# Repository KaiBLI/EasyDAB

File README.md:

# EasyDABv2
Repository of Plain-English Information for Sergiy's EasyDABv2 DAB Exciter Board. This is not to be confused with the EasyDABv1 which is a USB-based DAB exciter board. The USB DAB Board requires a computer to handle modulation while the v2 board utilizes a FPGA for independent operation.

# Introducton
First off, much of this is not my original work, credit goes to Sergiy for the design and release of the EasyDAB board. His site can be found here: https://tipok.org.ua/node/46

Secondly, this is a repository of the information I've learned through trying to manufacture one of these boards myself in order that folks in the future have an easier time with it than me.
There are a couple of issues with the original release of this board, firstly, I have not been able to find a license or any information regarding copyright of this board. Given that this was done in collaboration with the OpenDigitalRadio group, it is assumed that the board was released under similar licensing to the other projects under OpenDigitalRadio, that is permitting deriative work which is also licensed under the GPL and with credit to the original creator. 

If the above is not correct and the board was released under a more restrictive license, please get in touch at hoosk@retrohoosk.tv and this repository will be updated as such. That being said, under no circumstances will documentation of my own making be removed that was created based on information that is publicly available. 

# Aims
As mentioned in the introduction, the information is somewhat sparse on how to go about creating one of these boards. The original release was an Eagle PCB project coupled with a release of the firmware for flashing the board. The rest is left up to the individual to 'figure it out' (tm). 

As I'm a believer in easy, accessible and transparent documentation railing against those that insist on spoon-feeding being a bad thing, I have determined to document my findings and provide as much information as possible regarding the manufacture and configuration of these boards. 

So the aims of this project encompass the following:
1. Documentation

I will proceed to create an 'info dump' of all of my findings that I've learned through building this projects.

2. Photos

I will proceed to create high-resolution and detailed photos of both empty boards and fully assembled units so that others can see what these look like once assembled.

3. A fresh bill of materials.

The existing bill of materials leave too much up to assumption, therefore I will create a digikey cart and an Excel sheet of components required including example part numbers. It is assumed that components over time will be obsoleted and substitutes will be required, hence specification of components will be detailed as possible.

4. New Features

The board already supports DRM and FM modulation in addition to DAB/DAB+, theortically additional FPGA core/firmware could be built for other digital modulation such as HDRadio/NRSC5 and DVB. 

5. Board redesign.

The existing board requires redesign, solder pads overlay over existing component lables, requiring continuous reference to the PCB layout in CAD during assembly. This leaves opportunity to mistake and damage of expensive components (I'm looking at that Analog Devices Digital Synthesiser!). The board also allows different options depending on whether you wish to use a Single Frequency Network, FM or Digital Radio Mondiale usage, whether to use the mini360 modules and whether to use the band-pass filter. Given that there is little need for this board to be compact, outside of manufactoring costs, additional space can be used to make component locations clearer to the average hobbyist.

# Contact
Questions and Comments can be directed to hoosk@retrohoosk.tv , I'd love to hear your experience with assembling one of these boards and other ideas for this repo.

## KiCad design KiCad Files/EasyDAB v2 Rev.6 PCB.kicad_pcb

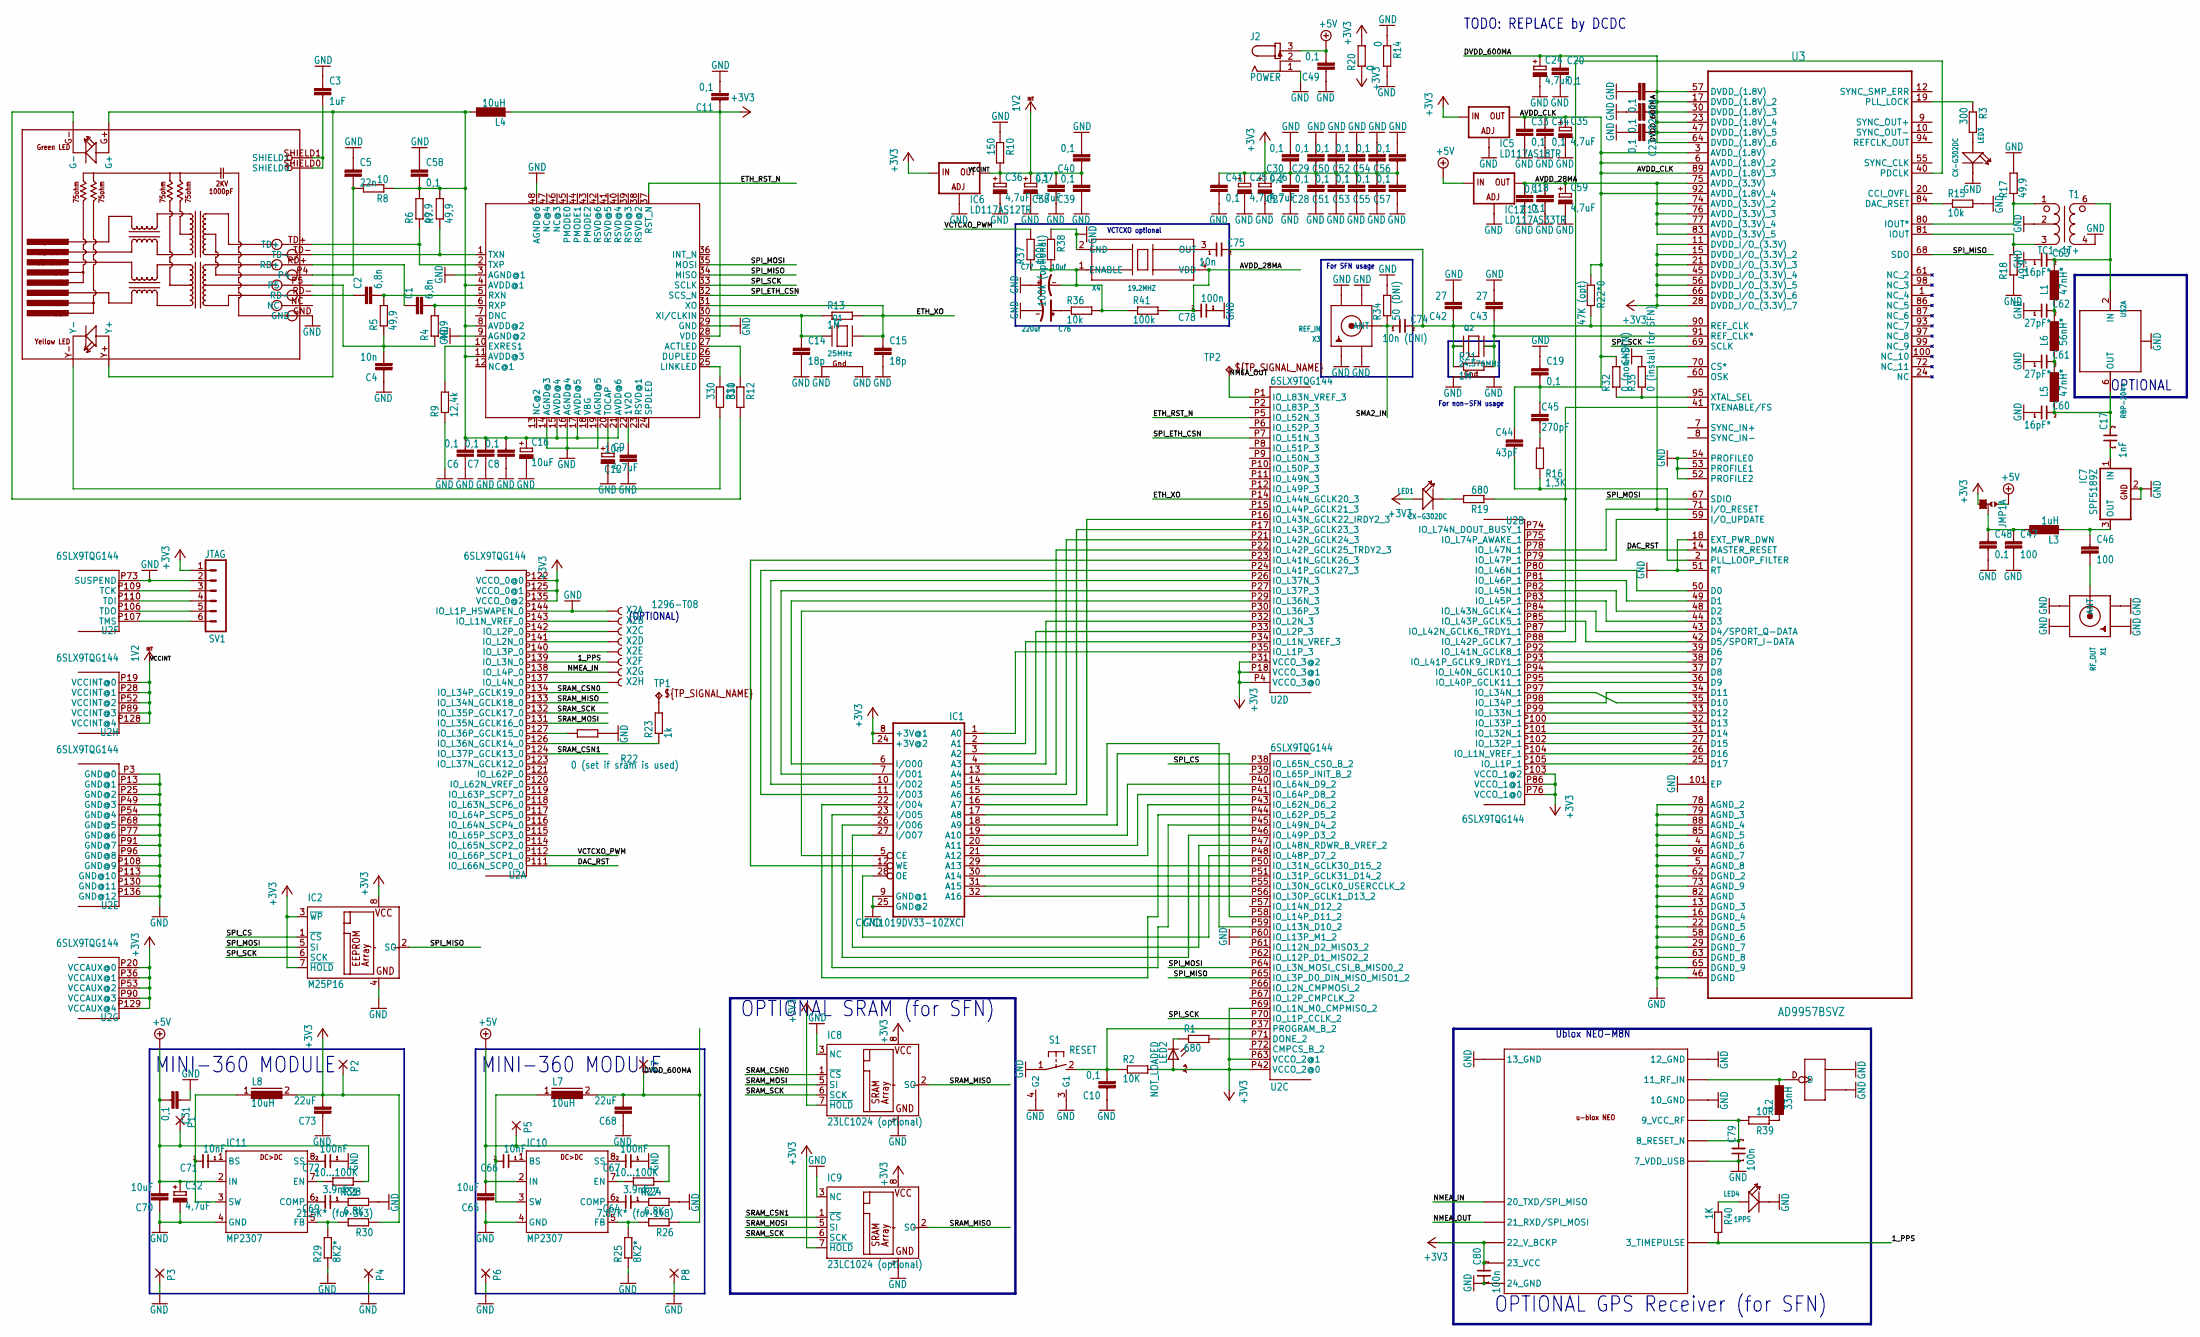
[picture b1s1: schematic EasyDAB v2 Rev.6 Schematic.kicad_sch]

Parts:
ANT1: U-FL; U-FL3P-SMD-2.6X2.6X1.0MM
C1, C2: 6,8n; C0805
C3: 1uF; C1206
C4, C12: 10n; C0805
C5: 22n; C0805
C6, C7, C8, C10, C11, C13, C18, C19, C20, C21, C22, C23, C27, C28, C29, C30, C31, C33, C34, C38, C39, C40, C41, C49, C50, C51, C52, C53, C54, C55, C56, C57, C58: 0,1; C0805
C9, C24, C25, C26, C32, C35, C36, C37, C59: 4,7uF; A_3216-18R
C14, C15: 18p; C0805
C16: 10uF; A_3216-18R
C17: 1nF; 0603
C42, C43: 27; C0805
C44: 43pF; C0805
C45: 270pF; C0805
C46, C47: 100; C0805
C48: 0.1; C0805
C60, C63: 16pF*; 0603
C61, C62: 27pF*; 0603
C64, C69: 3.9nF; 0603
C65, C70: 10uF; C1206
C66, C71: 10nF; 0603
C67, C72: 100nF; 0603
C68, C73: 22uF; C1206
C74: 10n (DNI); 0603
C75: 10n; 0603
C76: 220uf; AVX-D
C77: 10uf; AVX-A
C78, C79, C80: 100n; 0603
IC1: CY7C1019DV33-10ZXCI; TSOPII-32
IC2: M25P16; SO-08
IC5: LD117AS18TR; SOT223
IC6: LD117AS12TR; SOT223
IC7: SPF5189Z; SOT89
IC8, IC9: 23LC1024 (optional); SO-08
IC10, IC11: MP2307; SO8
IC12: LD117AS33TR; SOT223
J2: POWER; SPC4077
JMP1: 0R-JUMPA; A0R-JMP
L1, L5: 47nH*; INDC1608X95N
L2: 33nH; INDC1608X95N
L3: 1uH; L3216C
L4: 10uH; L3216C
L6: 56nH*; INDC1608X95N
L7, L8: 10uH; DR74
LED1, LED3: CX-G302DC; LED2-2.54-D3.0MM
LED2: NOT_LOADED; CHIPLED_1206
LED4: 1PPS; LED2-2.54-D3.0MM
P1, P2, P3, P4, P5, P6, P7, P8: 1,6/0,8; 1,6_0,8
Q1: 25MHz; NX3225
Q2: 24.576MHz; NX3225
R1, R19: 680; M0805
R2: 10K; M0805
R3: 300; M0805
R4, R5, R6, R7, R17, R18: 49,9; R0805
R8: 10; R0805
R9: 12,4k; R0805
R10: 150; R0805
R11, R12: 330; R0805
R13, R21: 1M; R0805
R14: 0; R0805
R15: 10k; R0805
R16: 1,3K; R0805
R20: 0; R1210
R22: 0 (set if sram is used); R0402
R22*0: 47K (opt); R0603
R23: 1k; R0603
R24, R28: 6.8K; R0603
R25, R29: 8K2*; R0603
R26: 7.87K* (for 1v8); R0603
R27, R31: 10...100K; R0603
R30: 21.5K* (for 3v3); R0603
R32: 0 (non-SFN); R0402
R33: 0 (install for SFN); R0402
R34: 50 (DNI); R0402
R36: 10k; R0603
R37, R41: 100k; R0603
R38: 100k (optional); R0603
R39: 10R; R0402
R40: 1K; R0402
RJ2: HR911105A
S1: RESET; B3F-31XX
SV1: JTAG; MA06-1
T1: TC1-1T+; AT224-3
TP1: PPS_IN; B1,27
TP2: UART_OUT; B1,27
U1: W5500
U2: 6SLX9TQG144; TQ144
U3: AD9957BSVZ; QFP50P1600X1600X120-101N
U$1: NEO-M8
U$2: RBP-204+; GP731
X1: RF_OUT; SMA90_DIP
X2: 1296-T08; 1296-08
X3: REF_IN; W5500_LX9_AD9957_SMA_EDGELAUNCH_UFL
X4: 19.2MHZ; X4-SMD-3.2X2.5X0.7MM

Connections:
1_PPS: R40.2, U2.P139 (IO_L3N_0), U$1.3 (3_TIMEPULSE), X2.6
+3V3: C11.1, C25.+, C26.+, C27.2, C28.2, C29.1, C30.1, C41.1, C50.1, C51.2, C52.1, C53.2, C54.1, C55.2, C56.1, C57.2, C73.2, C80.2, IC1.8 (+3V@1), IC1.24 (+3V@2), IC2.3 (~WP), IC2.7 (~HOLD), IC2.8 (VCC), IC5.3 (IN), IC6.3 (IN), IC8.7 (~HOLD), IC8.8 (VCC), IC9.7 (~HOLD), IC9.8 (VCC), JMP1.3, L4.2, L8.2, LED1.A (+), LED2.A, P2.1, R2.2, R20.1, R20.2, R30.1, SV1.1, U1.28 (VDD), U2.P4 (VCCO_3@0), U2.P18 (VCCO_3@1), U2.P20 (VCCAUX@0), U2.P31 (VCCO_3@2), U2.P36 (VCCAUX@1), U2.P42 (VCCO_2@0), U2.P53 (VCCAUX@2), U2.P63 (VCCO_2@1), U2.P69 (IO_L1N_M0_CMPMISO_2), U2.P76 (VCCO_1@0), U2.P86 (VCCO_1@1), U2.P90 (VCCAUX@3), U2.P103 (VCCO_1@2), U2.P122 (VCCO_0@0), U2.P125 (VCCO_0@1), U2.P129 (VCCAUX@4), U2.P135 (VCCO_0@2), U3.11 (DVDD_I/O_(3.3V)), U3.15 (DVDD_I/O_(3.3V)_2), U3.21 (DVDD_I/O_(3.3V)_3), U3.28 (DVDD_I/O_(3.3V)_7), U3.45 (DVDD_I/O_(3.3V)_4), U3.56 (DVDD_I/O_(3.3V)_5), U3.66 (DVDD_I/O_(3.3V)_6), U$1.22 (22_V_BCKP), U$1.23 (23_VCC)
+5V: C31.2, C32.+, C49.2, C65.2, C70.2, IC10.2 (IN), IC11.2 (IN), IC12.3 (IN), J2.3, JMP1.1, P1.1, P5.1, R27.1, R31.1
AVDD_28MA: C13.2, C18.1, C59.+, C78.2, IC12.4 (OUT), R41.2, U3.74 (AVDD_(3.3V)_2), U3.75 (AVDD_(3.3V)), U3.76 (AVDD_(3.3V)_3), U3.77 (AVDD_(3.3V)_4), U3.83 (AVDD_(3.3V)_5), X4.4 (VDD)
AVDD_CLK: C19.2, C33.1, C34.1, C35.+, C44.1, C45.1, IC5.4 (OUT), R22*0.1, R32.2, U3.3 (AVDD_(1.8V)), U3.6 (AVDD_(1.8V)_2), U3.89 (AVDD_(1.8V)_3), U3.92 (AVDD_(1.8V)_4)
AVDD_ETH: C6.2, C7.2, C8.2, C16.+, C58.2, L4.1, R6.2, R7.2, R8.1, RJ2.G+, RJ2.Y+, U1.4 (AVDD@1), U1.8 (AVDD@2), U1.11 (AVDD@3), U1.15 (AVDD@4), U1.17 (AVDD@5), U1.21 (AVDD@6)
DAC_RST: U2.P111 (IO_L66N_SCP0_0), U3.14 (MASTER_RESET)
DVDD_600MA: C20.1, C21.1, C22.1, C23.1, C24.+, C68.2, L7.2, P7.1, R26.1, U3.17 (DVDD_(1.8V)_2), U3.23 (DVDD_(1.8V)_4), U3.30 (DVDD_(1.8V)_3), U3.47 (DVDD_(1.8V)_5), U3.57 (DVDD_(1.8V)), U3.64 (DVDD_(1.8V)_6)
ETH_RST_N: U1.37 (RST_N), U2.P5 (IO_L52N_3)
ETH_XO: C15.1, Q1.3 (X2), R13.2, U1.31 (XO), U2.P14 (IO_L44N_GCLK20_3)
GND: ANT1.GND1, ANT1.GND2, C3.1, C4.1, C5.1, C6.1, C7.1, C8.1, C9.-, C10.1, C11.2, C12.1, C13.1, C14.2, C15.2, C16.-, C18.2, C19.1, C20.2, C21.2, C22.2, C23.2, C24.-, C25.-, C26.-, C27.1, C28.1, C29.2, C30.2, C31.1, C32.-, C33.2, C34.2, C35.-, C36.-, C37.-, C38.1, C39.1, C40.2, C41.2, C42.2, C43.2, C47.2, C48.2, C49.1, C50.2, C51.1, C52.2, C53.1, C54.2, C55.1, C56.2, C57.1, C58.1, C59.-, C60.1, C61.1, C62.1, C63.1, C65.1, C67.1, C68.1, C70.1, C72.1, C73.1, C76.-, C77.+, C78.1, C79.1, C80.1, IC1.9 (GND@1), IC1.25 (GND@2), IC2.4 (GND), IC5.1 (ADJ), IC6.1 (ADJ), IC7.2 (GND), IC7.2@1 (GND@1), IC8.3 (NC), IC8.4 (GND), IC9.3 (NC), IC9.4 (GND), IC10.4 (GND), IC11.4 (GND), IC12.1 (ADJ), J2.1, LED3.K (-), LED4.K (-), P3.1, P4.1, P6.1, P8.1, Q1.2 (G2), Q1.4 (G1), Q2.2 (G2), Q2.4 (G1), R9.1, R10.1, R14.1, R14.2, R15.2, R17.2, R18.1, R22.1, R24.2, R25.1, R28.2, R29.1, R33.2, R34.2, R38.1, RJ2.GND, S1.1, S1.3 (G1), S1.4 (G2), SV1.2, T1.2 (SCT), T1.4, U1.3 (AGND@1), U1.9 (AGND@2), U1.14 (AGND@3), U1.16 (AGND@4), U1.19 (AGND@5), U1.29 (GND), U1.48 (AGND@6), U2.P3 (GND@0), U2.P13 (GND@1), U2.P25 (GND@2), U2.P49 (GND@3), U2.P54 (GND@4), U2.P60 (IO_L13P_M1_2), U2.P68 (GND@5), U2.P73 (SUSPEND), U2.P77 (GND@6), U2.P91 (GND@7), U2.P96 (GND@8), U2.P108 (GND@9), U2.P113 (GND@10), U2.P130 (GND@11), U2.P136 (GND@12), U2.P144 (IO_L1P_HSWAPEN_0), U3.4 (AGND_6), U3.5 (AGND_8), U3.13 (DGND_3), U3.16 (DGND_4), U3.18 (EXT_PWR_DWN), U3.22 (DGND_5), U3.29 (DGND_7), U3.46 (DGND), U3.51 (RT), U3.52 (PROFILE2), U3.53 (PROFILE1), U3.54 (PROFILE0), U3.58 (DGND_6), U3.62 (DGND_2), U3.63 (DGND_8), U3.65 (DGND_9), U3.73 (AGND_9), U3.78 (AGND_2), U3.79 (AGND_3), U3.82 (AGND), U3.85 (AGND_5), U3.88 (AGND_4), U3.96 (AGND_7), U3.101 (EP), U$1.7 (7_VDD_USB), U$1.10 (10_GND), U$1.12 (12_GND), U$1.13 (13_GND), U$1.24 (24_GND), U$2.1 (GND), U$2.3 (GND), U$2.4 (GND), U$2.5 (GND), U$2.7 (GND), U$2.8 (GND), X1.GND1, X1.GND2, X1.GND3, X1.GND4, X2.1, X3.GND@1 (GND1), X3.GND@2 (GND2), X3.GND@3 (GND3), X3.GND@4 (GND4), X4.2 (GND)
unnamed: SV1.6, U2.P107 (TMS)
unnamed: SV1.5, U2.P106 (TDO)
unnamed: SV1.4, U2.P110 (TDI)
unnamed: SV1.3, U2.P109 (TCK)
unnamed: LED2.C, R1.1
unnamed: R1.2, U2.P71 (DONE_2)
unnamed: U2.P105 (IO_L1P_1), U3.25 (D17)
unnamed: C10.2, R2.1, S1.2 (S), U2.P37 (PROGRAM_B_2)
unnamed: U2.P88 (IO_L42P_GCLK7_1), U3.40 (PDCLK)
unnamed: R19.1, U2.P87 (IO_L42N_GCLK6_TRDY1_1), U3.41 (TXENABLE/FS)
unnamed: U2.P85 (IO_L43P_GCLK5_1), U3.42 (D5/SPORT_I-DATA)
unnamed: U2.P84 (IO_L43N_GCLK4_1), U3.43 (D4/SPORT_Q-DATA)
unnamed: U2.P83 (IO_L45P_1), U3.44 (D3)
unnamed: U2.P82 (IO_L45N_1), U3.48 (D2)
unnamed: U2.P92 (IO_L41N_GCLK8_1), U3.39 (D6)
unnamed: U2.P93 (IO_L41P_GCLK9_IRDY1_1), U3.38 (D7)
unnamed: U2.P94 (IO_L40N_GCLK10_1), U3.37 (D8)
unnamed: U2.P95 (IO_L40P_GCLK11_1), U3.36 (D9)
unnamed: U2.P98 (IO_L34P_1), U3.34 (D11)
unnamed: U2.P97 (IO_L34N_1), U3.35 (D10)
unnamed: U2.P99 (IO_L33N_1), U3.33 (D12)
unnamed: U2.P100 (IO_L33P_1), U3.32 (D13)
unnamed: U2.P101 (IO_L32N_1), U3.31 (D14)
unnamed: U2.P102 (IO_L32P_1), U3.27 (D15)
unnamed: U2.P104 (IO_L1N_VREF_1), U3.26 (D16)
unnamed: U2.P79 (IO_L47P_1), U3.59 (I/O_UPDATE)
unnamed: U2.P78 (IO_L47N_1), U3.70 (CS*), U3.71 (I/O_RESET)
unnamed: U2.P81 (IO_L46P_1), U3.49 (D1)
unnamed: LED3.A (+), R3.2
unnamed: R3.1, U3.19 (PLL_LOCK)
unnamed: R15.1, U3.84 (DAC_RSET)
unnamed: R17.1, T1.1 (SD), U3.80 (IOUT*)
unnamed: R18.2, T1.3 (S), U3.81 (IOUT)
unnamed: C63.2, L1.2, T1.6 (PD), U$2.2 (IN)
unnamed: U2.P80 (IO_L46N_1), U3.50 (D0)
unnamed: IC1.32 (A16), U2.P56 (IO_L30P_GCLK1_D13_2)
unnamed: IC1.31 (A15), U2.P55 (IO_L30N_GCLK0_USERCCLK_2)
unnamed: IC1.30 (A14), U2.P51 (IO_L31P_GCLK31_D14_2)
unnamed: IC1.29 (A13), U2.P50 (IO_L31N_GCLK30_D15_2)
unnamed: IC1.28 (OE), U2.P48 (IO_L48P_D7_2)
unnamed: IC1.27 (I/O07), U2.P47 (IO_L48N_RDWR_B_VREF_2)
unnamed: IC1.26 (I/O06), U2.P46 (IO_L49P_D3_2)
unnamed: IC1.1 (A0), U2.P35 (IO_L1P_3)
unnamed: IC1.23 (I/O05), U2.P45 (IO_L49N_D4_2)
unnamed: IC1.22 (I/O04), U2.P44 (IO_L62P_D5_2)
unnamed: IC1.21 (A12), U2.P43 (IO_L62N_D6_2)
unnamed: IC1.20 (A11), U2.P41 (IO_L64P_D8_2)
unnamed: IC1.19 (A10), U2.P40 (IO_L64N_D9_2)
unnamed: IC1.18 (A9), U2.P58 (IO_L14P_D11_2)
unnamed: IC1.17 (A8), U2.P59 (IO_L13N_D10_2)
unnamed: IC1.2 (A1), U2.P34 (IO_L1N_VREF_3)
unnamed: IC1.3 (A2), U2.P33 (IO_L2P_3)
unnamed: IC1.4 (A3), U2.P32 (IO_L2N_3)
unnamed: IC1.13 (A4), U2.P22 (IO_L42P_GCLK25_TRDY2_3)
unnamed: IC1.12 (WE), U2.P23 (IO_L41N_GCLK26_3)
unnamed: IC1.14 (A5), U2.P21 (IO_L42N_GCLK24_3)
unnamed: IC1.15 (A6), U2.P17 (IO_L43P_GCLK23_3)
unnamed: IC1.11 (I/O03), U2.P24 (IO_L41P_GCLK27_3)
unnamed: IC1.10 (I/O02), U2.P26 (IO_L37N_3)
unnamed: IC1.7 (I/O01), U2.P27 (IO_L37P_3)
unnamed: IC1.6 (I/O00), U2.P29 (IO_L36N_3)
unnamed: IC1.16 (A7), U2.P16 (IO_L43N_GCLK22_IRDY2_3)
unnamed: IC1.5 (CE), U2.P30 (IO_L36P_3)
unnamed: R7.1, RJ2.TD-, U1.1 (TXN)
unnamed: R6.1, RJ2.TD+, U1.2 (TXP)
unnamed: C1.1, RJ2.RD+
unnamed: C1.2, R4.2, U1.6 (RXP)
unnamed: C2.2, R5.2, U1.5 (RXN)
unnamed: C2.1, RJ2.RD-
unnamed: C3.2, RJ2.SHIELD0, RJ2.SHIELD1
unnamed: C4.2, R4.1, R5.1, RJ2.P5
unnamed: C12.2, U1.22 (1V2O)
unnamed: C5.2, R8.2, RJ2.P4
unnamed: R22.2, U2.P127 (IO_L36P_GCLK15_0)
unnamed: R23.2, TP1.TP
unnamed: C9.+, U1.20 (TOCAP)
unnamed: C44.2, R16.2, U3.2 (PLL_LOOP_FILTER)
unnamed: R9.2, U1.10 (EXRES1)
unnamed: R11.1, U1.25 (LINKLED)
unnamed: R12.1, U1.27 (ACTLED)
unnamed: R11.2, RJ2.Y-
unnamed: R12.2, RJ2.G-
unnamed: C14.1, Q1.1 (X1), R13.1, U1.30 (XI/CLKIN)
unnamed: C45.2, R16.1
unnamed: C17.2, C60.2, L5.1, U$2.6 (OUT)
unnamed: C46.1, IC7.3 (OUT), L3.2
unnamed: C46.2, X1.ANTENNA (ANT)
unnamed: C47.1, C48.1, JMP1.2, L3.1
unnamed: LED1.K (-), R19.2
unnamed: L2.1, R39.1
unnamed: C61.2, L5.2, L6.1
unnamed: R23.1, U2.P126 (IO_L36N_GCLK14_0)
unnamed: C79.2, R39.2, U$1.8 (8_RESET_N), U$1.9 (9_VCC_RF)
unnamed: LED4.A (+), R40.1
unnamed: U2.P141 (IO_L2N_0), X2.4
unnamed: U2.P140 (IO_L3P_0), X2.5
unnamed: U2.P137 (IO_L4N_0), X2.8
unnamed: C62.2, L1.1, L6.2
unnamed: C17.1, IC7.1 (IN)
unnamed: C64.2, IC10.6 (COMP)
unnamed: C64.1, R24.1
unnamed: C66.1, IC10.1 (BS)
unnamed: C66.2, IC10.3 (SW), L7.1
unnamed: C67.2, IC10.8 (SS)
unnamed: IC10.5 (FB), R25.2, R26.2
unnamed: R32.1, R33.1, U3.95 (XTAL_SEL)
unnamed: IC10.7 (EN), R27.2
unnamed: C69.1, R28.1
unnamed: C69.2, IC11.6 (COMP)
unnamed: C71.1, IC11.1 (BS)
unnamed: C71.2, IC11.3 (SW), L8.1
unnamed: C72.2, IC11.8 (SS)
unnamed: IC11.5 (FB), R29.2, R30.2
unnamed: IC11.7 (EN), R31.2
unnamed: C76.+, R36.1
unnamed: C77.-, R36.2, R37.1, R38.2, R41.1, X4.1 (ENABLE)
unnamed: ANT1.D, L2.2, U$1.11 (11_RF_IN)
unnamed: C75.1, X4.3 (OUT)
NMEA_IN: U2.P138 (IO_L4P_0), U$1.20 (20_TXD/SPI_MISO), X2.7
NMEA_OUT: TP2.TP, U2.P1 (IO_L83N_VREF_3), U$1.21 (21_RXD/SPI_MOSI)
SMA2_IN: C74.1, R34.1, X3.P (ANT)
SPIRAM_PIN: U2.P143 (IO_L1N_VREF_0), X2.2
SPIRAM_PINX: U2.P142 (IO_L2P_0), X2.3
SPI_CS: IC2.1 (~CS), U2.P38 (IO_L65N_CSO_B_2)
SPI_ETH_CSN: U1.32 (SCS_N), U2.P7 (IO_L51N_3)
SPI_MISO: IC2.2 (SO), U1.34 (MISO), U2.P65 (IO_L3P_D0_DIN_MISO_MISO1_2), U3.68 (SDO)
SPI_MOSI: IC2.5 (SI), U1.35 (MOSI), U2.P64 (IO_L3N_MOSI_CSI_B_MISO0_2), U3.67 (SDIO)
SPI_SCK: IC2.6 (SCK), U1.33 (SCLK), U2.P70 (IO_L1P_CCLK_2), U3.69 (SCLK)
SRAM_CSN0: IC8.1 (~CS), U2.P134 (IO_L34P_GCLK19_0)
SRAM_CSN1: IC9.1 (~CS), U2.P124 (IO_L37P_GCLK13_0)
SRAM_MISO: IC8.2 (SO), IC9.2 (SO), U2.P133 (IO_L34N_GCLK18_0)
SRAM_MOSI: IC8.5 (SI), IC9.5 (SI), U2.P131 (IO_L35N_GCLK16_0)
SRAM_SCK: IC8.6 (SCK), IC9.6 (SCK), U2.P132 (IO_L35P_GCLK17_0)
VCCINT: C36.+, C37.+, C38.2, C39.2, C40.1, IC6.4 (OUT), R10.2, U2.P19 (VCCINT@0), U2.P28 (VCCINT@1), U2.P52 (VCCINT@2), U2.P89 (VCCINT@3), U2.P128 (VCCINT@4)
VCTCXO_PWM: R37.2, U2.P112 (IO_L66P_SCP1_0)
XTALI: C42.1, C74.2, C75.2, Q2.1 (X1), R21.1, R22*0.2, U3.90 (REF_CLK)
XTALO: C43.1, Q2.3 (X2), R21.2, U3.91 (REF_CLK*)

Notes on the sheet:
MINI-360 MODULE
Ublox NEO-M8N
OPTIONAL GPS Receiver (for SFN)
VCTCXO optional
TODO: REPLACE by DCDC
For non-SFN usage
(OPTIONAL)
OPTIONAL SRAM (for SFN)
OPTIONAL
For SFN usage

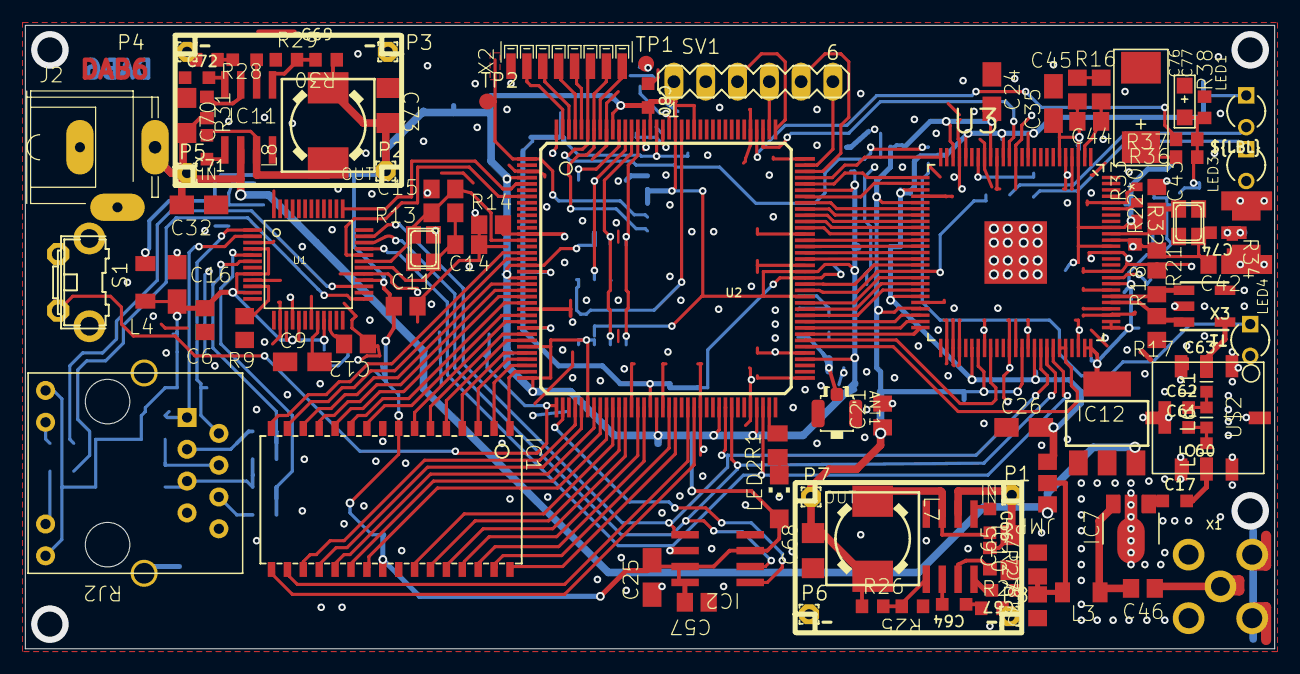
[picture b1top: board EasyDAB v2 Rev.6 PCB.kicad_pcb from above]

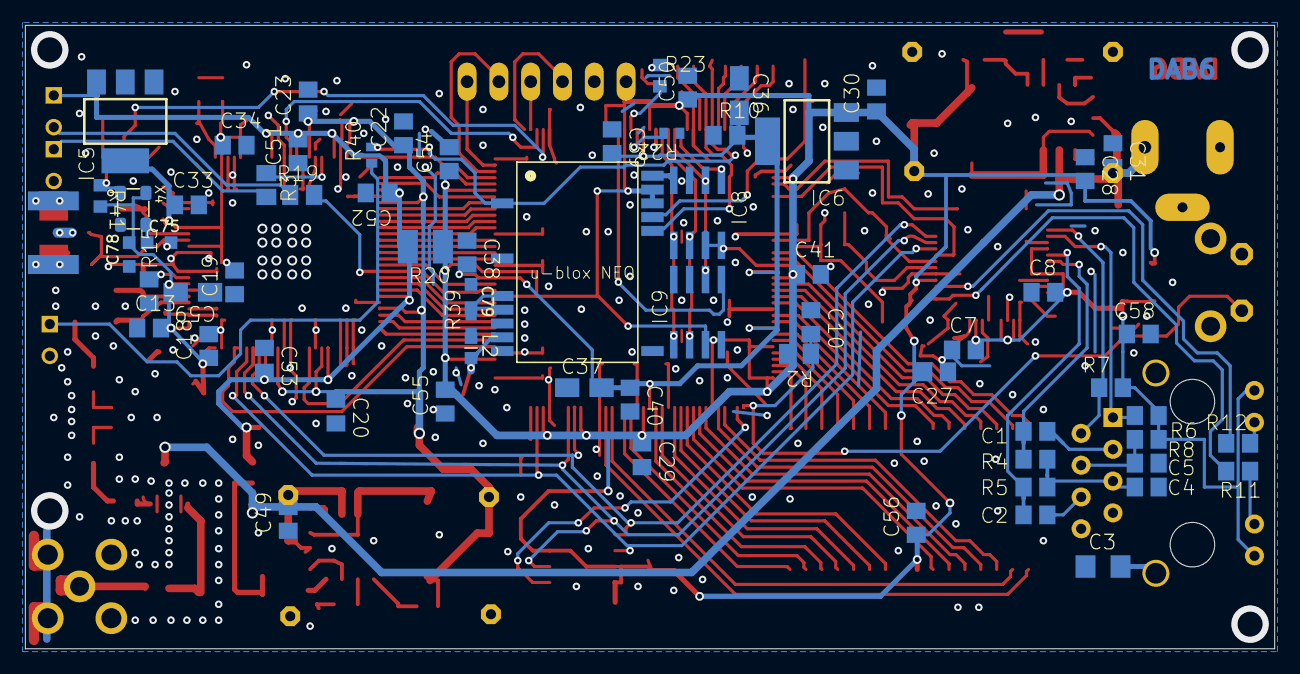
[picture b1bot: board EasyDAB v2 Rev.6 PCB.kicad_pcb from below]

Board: 2 copper layers, 99.8 x 49.8 mm, 171 parts (65 on the bottom side), 148 nets.

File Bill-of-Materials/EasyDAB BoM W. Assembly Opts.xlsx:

Reference Designators | Quantity | Description | Package | Value | Manufacturer P/N | Comments | Vendor | Vendor Part Number | Top/Bottom
C1 | 1 | CAPACITOR | C0805 | 6.8 nF |  |  |  |  | Bottom
C10 | 1 | CAPACITOR | C0805 | 0.1 uF |  |  |  |  | Bottom
C11 | 1 | CAPACITOR | C0805 | 0.1 uF |  |  |  |  | Top
C12 | 1 | CAPACITOR | C0805 | 10 nF |  |  |  |  | Top
C13 | 1 | CAPACITOR | C0805 | 0.1 uF |  |  |  |  | Bottom
C14 | 1 | CAPACITOR | C0805 | 18pF |  |  |  |  | Top
C15 | 1 | CAPACITOR | C0805 | 18 pF |  |  |  |  | Top
C16 | 1 | Chip Capacitor Type KEMET A / EIA 3216-18 reflow solderKEMET S / EIA 3216-12 | A/3216-18R | 10 uF |  |  |  |  | Top
C17 | 1 | SMD CHIP CAP | 0603 | 1 nF |  |  |  |  | Top
C18 | 1 | CAPACITOR | C0805 | 0.1 uF |  |  |  |  | Bottom
C19 | 1 | CAPACITOR | C0805 | 0.1 uF |  |  |  |  | Bottom
C2 | 1 | CAPACITOR | C0805 | 6.8 nF |  |  |  |  | Bottom
C20 | 1 | CAPACITOR | C0805 | 0.1 uF |  |  |  |  | Bottom
C21 | 1 | CAPACITOR | C0805 | 0.1 uF |  |  |  |  | Top
C22 | 1 | CAPACITOR | C0805 | 0.1 uF |  |  |  |  | Bottom
C23 | 1 | CAPACITOR | C0805 | 0.1 uF |  |  |  |  | Bottom
C24 | 1 | Chip Capacitor Type KEMET A / EIA 3216-18 reflow solderKEMET S / EIA 3216-12 | A/3216-18R | 4.7 uF |  |  |  |  | Top
C25 | 1 | Chip Capacitor Type KEMET A / EIA 3216-18 reflow solderKEMET S / EIA 3216-12 | A/3216-18R | 4.7 uF |  |  |  |  | Top
C26 | 1 | Chip Capacitor Type KEMET A / EIA 3216-18 reflow solderKEMET S / EIA 3216-12 | A/3216-18R | 4.7uF |  |  |  |  | Top
C27 | 1 | CAPACITOR | C0805 | 0.1 uF |  |  |  |  | Bottom
C28 | 1 | CAPACITOR | C0805 | 0.1 uF |  |  |  |  | Bottom
C29 | 1 | CAPACITOR | C0805 | 0.1 uF |  |  |  |  | Bottom
C3 | 1 | CAPACITOR | C1206 | 1uF |  |  |  |  | Bottom
C30 | 1 | CAPACITOR | C0805 | 0.1 uF |  |  |  |  | Bottom
C33 | 1 | CAPACITOR | C0805 | 0.1 uF |  |  |  |  | Bottom
C34 | 1 | CAPACITOR | C0805 | 0.1 uF |  |  |  |  | Bottom
C35 | 1 | Chip Capacitor Type KEMET A / EIA 3216-18 reflow solderKEMET S / EIA 3216-12 | A/3216-18R | 4.7 uF |  |  |  |  | Top
C36 | 1 | Chip Capacitor Type KEMET A / EIA 3216-18 reflow solderKEMET S / EIA 3216-12 | A/3216-18R | 4.7 uF |  |  |  |  | Bottom
C37 | 1 | Chip Capacitor Type KEMET A / EIA 3216-18 reflow solderKEMET S / EIA 3216-12 | A/3216-18R | 4.7 uF |  |  |  |  | Bottom
C38 | 1 | CAPACITOR | C0805 | 0.1 uF |  |  |  |  | Bottom
C39 | 1 | CAPACITOR | C0805 | 0.1 uF |  |  |  |  | Bottom
C4 | 1 | CAPACITOR | C0805 | 10 nF |  |  |  |  | Bottom
C40 | 1 | CAPACITOR | C0805 | 0.1 uF |  |  |  |  | Bottom
C41 | 1 | CAPACITOR | C0805 | 0.1 uF |  |  |  |  | Bottom
C42 | 1 | CAPACITOR | C0805 | 27pF |  |  |  |  | Top
C43 | 1 | CAPACITOR | C0805 | 27pF |  |  |  |  | Top
C44 | 1 | CAPACITOR | C0805 | 43 pF |  |  |  |  | Top
C45 | 1 | CAPACITOR | C0805 | 270 pF |  |  |  |  | Top
C46 | 1 | CAPACITOR | C0805 | 100 pF |  |  |  |  | Top
C47 | 1 | CAPACITOR | C0805 | 100 pF |  |  |  |  | Top
C48 | 1 | CAPACITOR | C0805 | 0.1 uF |  |  |  |  | Top
C49 | 1 | CAPACITOR | C0805 | 0.1 uF |  |  |  |  | Bottom
C5 | 1 | CAPACITOR | C0805 | 22 nF |  |  |  |  | Bottom
C50 | 1 | CAPACITOR | C0805 | 0.1 uF |  |  |  |  | Bottom
C51 | 1 | CAPACITOR | C0805 | 0.1 uF |  |  |  |  | Bottom
C52 | 1 | CAPACITOR | C0805 | 0.1 uF |  |  |  |  | Bottom
C53 | 1 | CAPACITOR | C0805 | 0.1 uF |  |  |  |  | Bottom
C54 | 1 | CAPACITOR | C0805 | 0.1 uF |  |  |  |  | Bottom
C55 | 1 | CAPACITOR | C0805 | 0.1 uF |  |  |  |  | Bottom
C56 | 1 | CAPACITOR | C0805 | 0.1 uF |  |  |  |  | Bottom
C57 | 1 | CAPACITOR | C0805 | 0.1 uF |  |  |  |  | Top
C58 | 1 | CAPACITOR | C0805 | 0.1 uF |  |  |  |  | Bottom
C59 | 1 | Chip Capacitor Type KEMET A / EIA 3216-18 reflow solderKEMET S / EIA 3216-12 | A/3216-18R | 4.7 uF |  |  |  |  | Bottom
C6 | 1 | CAPACITOR | C0805 | 0.1 uF |  |  |  |  | Top
C7 | 1 | CAPACITOR | C0805 | 0.1 uF |  |  |  |  | Bottom
C74 | 1 | SMD CHIP CAP | 0603 | 10 nF (DNI) |  |  |  |  | Top
C8 | 1 | CAPACITOR | C0805 | 0.1 uF |  |  |  |  | Bottom
C9 | 1 | Chip Capacitor Type KEMET A / EIA 3216-18 reflow solderKEMET S / EIA 3216-12 | A/3216-18R | 4.7 uF |  |  |  |  | Top
IC1 | 1 | 32-pin TSOP II (51-85095) – Voltage Reglator | TSOPII-32 | CY7C1019DV33-10ZXCI |  | Main SRAM for FPGA |  |  | Top
IC12 | 1 | Small Outline Transistor 223 | SOT223 | LD117AS33TR |  | Voltage Regulator |  |  | Top
IC2 | 1 | Small Outline Narrow Plastic Gull Wing – SPI Flash | SO-08 | M25P16 | 25LC080/SN | SPI Flash for FPGA Bitstream |  |  | Top
IC5 | 1 | Small Outline Transistor 223 – Voltage Regulator | SOT223 | LD117AS18TR |  | Voltage Regulator |  |  | Bottom
IC6 | 1 | Small Outline Transistor 223 – Voltage Regulator | SOT223 | LD117AS12TR |  | Voltage Regulator |  |  | Bottom
IC7 | 1 | SOT98 PK (R-PDSO-G3) Low Noise Amplifier | SOT89 | SPF5189Z |  | Low Noise Amplifier to Step up RF |  |  | Top
J2 | 1 | DC POWER JACK 2mm Right Angle, Through Hole, Rated 5A at 16VDC, PC Terminals | SPC4077 | POWER |  | DC Barrel Jack |  |  | Top
JMP1 | 1 | 0R Jumper Variant A | A0R-JMP | 0R-JUMPA |  | 3.3 / 5v Jumper for Antenna Power |  |  | Top
L3 | 1 | INDUCTOR | L3216C | 1 uH |  |  |  |  | Top
L4 | 1 | INDUCTOR | L3216C | 1 uH |  |  |  |  | Top
LED1 | 1 | LED | LED2-2.54-D3.0MM | CX-G302DC | CX-G302DC | ETI Not Ready LED |  |  | Top
LED2 | 1 | CHIPLED | CHIPLED_1206 | NOT_LOADED |  | Empty FPGA Warning LED |  |  | Top
LED3 | 1 | LED | LED2-2.54-D3.0MM | CX-G302DC | CX-G302DC | PLL Lock LED |  |  | Top
Q1 | 1 | FPGA Oscillator | NX3225 | 25MHz |  | Drives FPGA at 25Mhz |  |  | Top
R1 | 1 | RESISTOR | M0805 | 680 Ohm |  |  |  |  | Top
R10 | 1 | RESISTOR | R0805 | 150 Ohm |  |  |  |  | Bottom
R11 | 1 | RESISTOR | R0805 | 330 Ohm |  |  |  |  | Bottom
R12 | 1 | RESISTOR | R0805 | 330 Ohm |  |  |  |  | Bottom
R13 | 1 | RESISTOR | R0805 | 1M Ohm |  |  |  |  | Top
R14 | 1 | RESISTOR | R0805 | 0 Ohm |  |  |  |  | Top
R15 | 1 | RESISTOR | R0805 | 10k Ohm |  |  |  |  | Bottom
R16 | 1 | RESISTOR | R0805 | 1.3K Ohm |  |  |  |  | Top
R17 | 1 | RESISTOR | R0805 | 49.9 Ohm |  |  |  |  | Top
R19 | 1 | RESISTOR | M0805 | 680 Ohm |  |  |  |  | Bottom
R2 | 1 | RESISTOR | M0805 | 10K Ohm |  |  |  |  | Bottom
R20 | 1 | RESISTOR | R1210 | 0 Ohm |  |  |  |  | Bottom
R22* | 1 | RESISTOR | R0603 | 47K Ohm(opt) |  |  |  |  | Top
R23 | 1 | RESISTOR | R0603 | 1k |  |  |  |  | Bottom
R3 | 1 | RESISTOR | M0805 | 300 Ohm |  |  |  |  | Bottom
R34 | 1 | RESISTOR | R0402 | 50 Ohm (DNI) |  |  |  |  | Top
R4 | 1 | RESISTOR | R0805 | 49.9 Ohm |  |  |  |  | Bottom
R5 | 1 | RESISTOR | R0805 | 49.9 Ohm |  |  |  |  | Bottom
R6 | 1 | RESISTOR | R0805 | 49.9 Ohm |  |  |  |  | Bottom
R7 | 1 | RESISTOR | R0805 | 49.9 Ohm |  |  |  |  | Bottom
R8 | 1 | RESISTOR | R0805 | 10 Ohm |  |  |  |  | Bottom
R9 | 1 | RESISTOR | R0805 | 12.4k Ohm |  |  |  |  | Top
RJ2 | 1 | RJ-45 Jack | HR911105A | HR911105A |  | Ethernet Jack |  |  | Top
S1 | 1 | OMRON SWITCH | B3F-31XX | RESET |  | Reset Switch |  |  | Top
T1 | 1 | RT TRANSFORMER | AT224-3 | TC1-1T+ |  | Mini Transformer to Step up RF |  |  | Top
U1 | 1 | Network Chip | W5500 | W5500 |  | Network Chip for TCP/IP and ETI |  |  | Top
U2 | 1 | FPGA TQ144 TQG144 | TQ144 | 6SLX9TQG144 |  | FPGA for Firmware and Modulation |  |  | Top
U3 | 1 | Digital Synthesizer | QFP50P1600X1600X120-101N | AD9957BSVZ |  | Digital Synth to Excite Digital RF |  |  | Top
X1 | 1 | SMA DIP Connector 90° 50 Ohm | SMA90_DIP | RF_OUT |  | Antenna Out |  |  | Top
X2 | 1 | 1.27mm SINGLE ROW FEMALE SOCKET | 1296-08 | 1296-T08 |  | FPGA JTAG |  |  | Top

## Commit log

2026-02-10 Update README.md
    Formatting fixes.
2026-02-10 Create Info-Dump
    Initial blurb.
2026-02-10 Update README.md
    Typo correction
2026-02-10 Rename Info-Dump.md to Assembly-Options.md
2026-02-10 Create High-Level-Explanation
2026-02-10 Create LICENSE
2026-02-11 Create Important Notes!
2026-02-18 Adding KiCad Converted PCB Map
2026-02-18 Adding EasyDAB v2 Board With Assembly Options BoM
2026-02-18 Adding PDF Version of Schematic
2026-02-18 Adding Correct Value for IC5
2026-02-19 Create DigiKey-Lists
2026-02-19 Adding Main Passives
2026-02-19 Adding Main ICs List
